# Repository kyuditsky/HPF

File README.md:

# Compact High Pass Filter 

- Designed for reading power line communications over 240V on oscilloscopes
- Input: (2) 4mm Safety Banana Jacks
- Output: BNC
- 18kHz cutoff
- 
- Kicad 6.0

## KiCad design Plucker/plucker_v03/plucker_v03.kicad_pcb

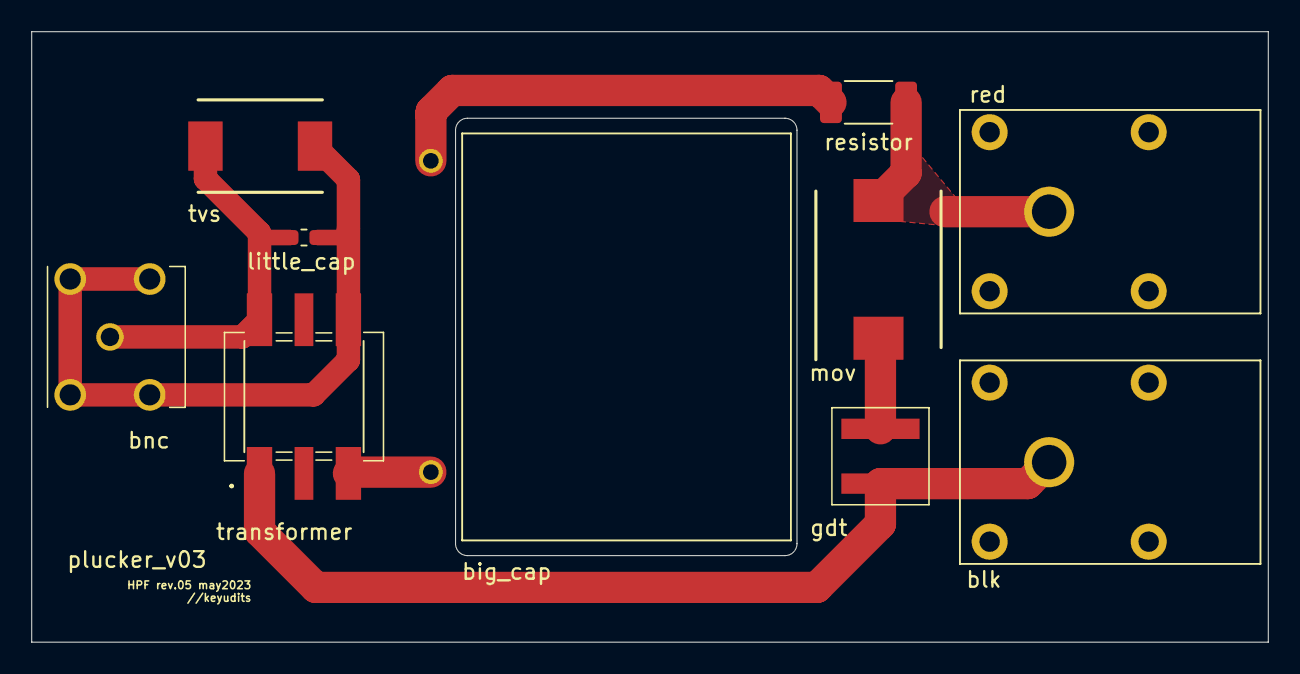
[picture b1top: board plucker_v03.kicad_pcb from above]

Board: 2 copper layers, 79.0 x 39.0 mm, 10 parts (0 on the bottom side), 7 nets.

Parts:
C1: ECQ-UBAF474K; ECQ-UBAF474K-3_side
C2: 220pF; C_0603_1608Metric_Pad1.05x0.95mm_HandSolder
D1: SMCJ918.0CA; littlefuseTVS
J1_BNC1: BNC5-J-P-GN-RA-BH2D; BNC5JPGNRABH2D
J2_BLACK1, J3_RED1: Conn_01x01; Banana_Jack_S_RA_73099
R1: 2.2; R_2010_5025Metric_Pad1.40x2.65mm_HandSolder
RV1: VP4032K122R300; MOV_VP4032K122R300
T1: GT07-110-013; GT07110013
U1: SL1002A600SP

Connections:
0: C2.1, D1.2, J1_BNC1.2, J1_BNC1.3, J1_BNC1.4, J1_BNC1.5, T1.4 (GATE_1)
unnamed: C1.1, R1.2
unnamed: C1.2, T1.3 (DRIVE_3)
unnamed: J2_BLACK1.1, T1.1 (DRIVE_1), U1.2
unnamed: RV1.1, U1.1
Out: C2.2, D1.1, J1_BNC1.1, T1.6 (GATE_3)
in: J3_RED1.1, R1.1, RV1.2

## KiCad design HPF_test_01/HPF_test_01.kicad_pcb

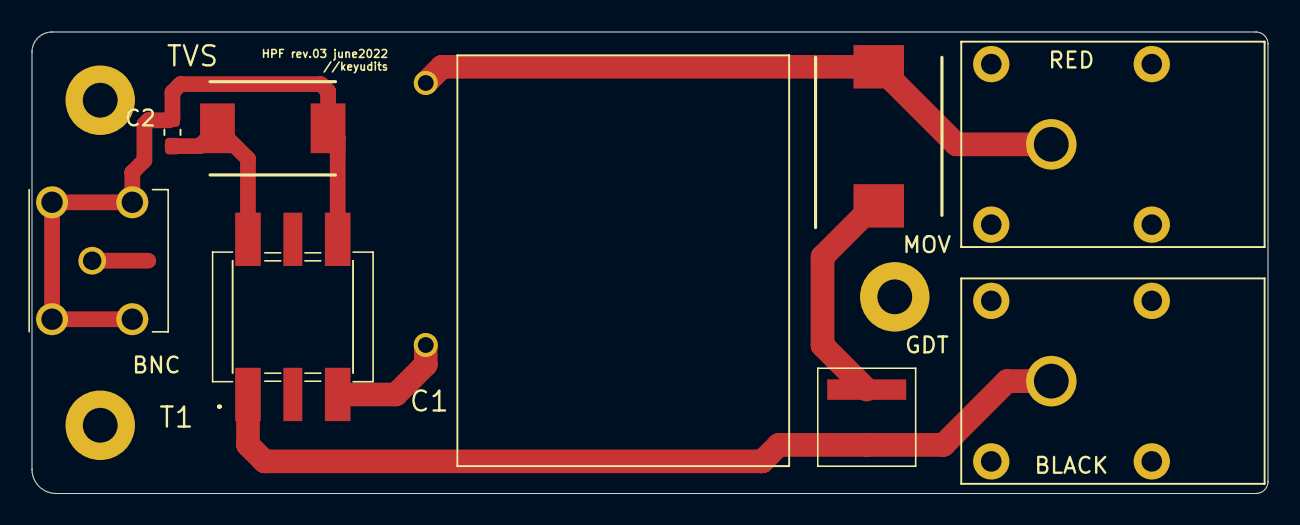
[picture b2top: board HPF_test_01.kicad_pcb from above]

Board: 2 copper layers, 78.2 x 29.2 mm, 9 parts (0 on the bottom side), 6 nets.

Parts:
BLACK: Conn_01x01; Banana_Jack_S_RA_73099
BNC: BNC5-J-P-GN-RA-BH2D; BNC5JPGNRABH2D
C1: ECQ-UBAF474K; ECQ-UBAF474K-3_side
C2: 220pF; C_0603_1608Metric_Pad1.05x0.95mm_HandSolder
GDT: SL1002A600SP
MOV: VP4032K122R300; CAPPM10080X500N
RED: Conn_01x01; Banana_Jack_S_RA_73099
T1: GT07-110-013; GT07110013
TVS: SMCJ5.0A; DIONM7959X262N

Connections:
unnamed: C1.1, MOV.2, RED.1
unnamed: C1.2, T1.6
unnamed: BNC.2, BNC.3, BNC.4, BNC.5, C2.1, T1.1, TVS.2
unnamed: BNC.1, C2.2, T1.3, TVS.1
unnamed: BLACK.1, GDT.2, T1.4
unnamed: GDT.1, MOV.1

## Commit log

2021-11-18 Added current project state
2021-11-28 Added xformer.lib
2021-11-29 Added GT07 .EPW spice model & Readme
2021-11-29 Added GT07 spice models from Library Loader
    Uploaded manually from Windows 10
2021-11-29 cleaning up repo, may backfire
2021-11-29 Replaced generic T1 with GT07 symbol
2021-12-18 added GDT, MOV, TVS, with specific components and datasheets
2021-12-27 Reorganized and added footprints and symbols, .sch reflects changes
2022-01-03 added pcbnew schematic and rudimentary layout
2022-01-03 Deleted .DS_Store
2022-01-03 Added **/.DS_Store to .gitignore
2022-01-03 Added modified GT07 footprint to accept T3001NL transformer
2022-01-04 Added Banana Jack footprint
2022-01-05 Updated Layout, added screenshots
2022-01-05 Added GT07 Spice Data.pdf
2022-01-06 PCB: Added traces, edgecuts, & accurate bananajack footprint. SPICE: Added spice data folders & updated eeschema simulation. 3D: Added 3d render folder and initial board render
2022-01-11 Modified 3D render, Added spice outputin test screenshots
2022-01-24 Turned C1 on its side to save space, updated footprint & board size, updated enclosure.
2022-02-01 Added clean .skp for import to fusion
2022-02-03 Added first .stl file and feb3 render png's
2022-02-03 Added Gerber files [hpf_test_01_gerber_v01]
2022-02-23 Added hpf_freeCAD & STL files
2022-06-07 moved to kicad 6.0
    includes minor revision to board layout, increase clearance between TVS & C1
2022-06-07 Update README.md
    Reflected Kicad version change
2023-03-13 Added Plucker_v02, layout for extruded case
2023-03-14 Added Pulse Proof Resistor
2023-05-30 Added plucker_v03
2023-10-16 assembled v03, added waveforms
2024-12-13 cleaned up repo folders, added pluckerv03 BOM & pricing sheet
